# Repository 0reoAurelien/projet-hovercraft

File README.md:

# RAPPORT HOVERCRAFT

## Introduction

Un hovercraft (en français aéroglisseur) est un véhicule amphibie à portance aérostatique et à propulsion aérienne, qui en général possède une ou plusieurs hélices aériennes. La portance est assurée par un coussin d'air sous faible pression relative, entretenu par une soufflante à l'intérieur d'une enceinte dont les parois latérales, appelées jupes, sont suffisamment déformables pour suivre au plus près le relief de la surface survolée et ainsi réduire les fuites. Les aéroglisseurs se déplacent le plus souvent sur la mer, mais aussi sur toute surface terrestre ne présentant pas d'obstacles importants.

Nous avons ainsi pour but d'en réaliser un avec le matériel proposé.

## Analyse technique du problème posé

|Objectifs à remplir|Contraintes|
|-------------------|-----------|
|Avancer, décoller|Pas de contrôle à distance (autonome)|
|Avancer "droit"|Pas de contrôle à distance (autonome)|
|Avancer 10m|Pas de contrôle à distance (autonome)|
|Avancer 10m le plus rapidement possible|Pas de contrôle à distance (autonome)|

Nous avons utilisé les composants suivants :
* 2 régulateurs de tension BUCK MAX5033 qui ont un fort rendement (entre 80 et 90%)
* Une centrale inertielle MPU6050
* Un microprocesseur STM32 qui communique en I2C avec la centrale inertielle
* 2 ESC qui communique en PWM avec le microprocesseur, les ESC contrôlent 2 moteurs
* Une batterie qui délivre une tension de 11,1 V
* Une sonde de programmation
* Un servo-moteur XL320 qui communique en UART avec le microprocesseur

Nous employons des régulateurs de tension afin d'adapter les niveaux de tension pour les composants utilisés. Le microprocesseur nécessite une tension de 3,3 V, tandis que la sonde de programmation requiert 7,4 V. Cependant, la batterie fournit une tension de 11,1 V.
Le microprocesseur lui sert à contrôler les ESC et donc les moteurs pour qu'on puisse accomplir les objectifs fixés. Le microprocesseur est complété par l'ajout du servo-moteur pour l'asservissement.
On a alors ce [diagramme](https://github.com/0reoAurelien/projet-hovercraft/blob/main/Hardware/DIAGRAMME_VF.png) qui résume cela.

L'I2C et l'UART sont des protocoles de communication. L'UART permet l'échange de données entre un émetteur et un récepeteur dans les 2 sens et l'I2C permet à un système maître de controler des systèmes esclaves.

## Méthodologie

Pour mener à bien ce projet, nous avons eu à utiliser plusieurs logiciels : 
* **Github** : logiciel qui nous permet de rassembler toute nos travaux dans un seul endroit
* **Draw.io** : logiciel qui nous permet de tracer des graphes
* **Redmine** : logiciel qui nous permet de nous créer un emploi du temps (diagramme de Gantt) et nous a permis de nous répartir les différentes taches
* **Kicad** : logiciel qui nous permet de faire nos schematic ainsi que nos PCB
* **STM32CubeIDE** : logiciel qui nous permet de programmer notre microprocesseur

Nous avons décidé de nous séparer en 2 groupes, un qui s'occupe de la partie hardware (conception de PCB et soudure) et l'autre qui s'occupe de la partie software.

## Problèmes rencontrés

Lorsque nous avons commencé à souder l'un de nos PCB, il y avait un problème de court-circuit entre la masse et du 3V3. Ce problème a pu être révélé grâce à la caméra thermique. Nous avons analysé notre PCB et déterminé qu'il s'agissait d'un défaut à la fabrication de la carte. Nous avons pu corriger le problème en coupant une zone du PCB pour retirer le court-circuit. Cependant nous avions aussi oublié le connecteur qui alimentait le système en 3V3 donc nous avons donc dû refaire une V2 de notre deuxième PCB.

Par mégarde, nous avons arraché un connecteur ce qui a arraché une piste cuivre de notre PCB. Nous avons réparé le problème en repositionnant la connecteur et en soudant un fil à la place du circuit arraché.
Lors de la réalisation du 2ème PCB concernant les régulateurs, nous avons rencontré des problèmes lors de la conception (notamment l'optimisation de la taille et certaines empreintes) et lors de la soudure de certains composants.

Durant l'étape de programmation, nous nous sommes heurtés à de nombreuses difficultés notamment sur les différents pins de sortie.
Nous avons divisé notre code en plusieurs parties. Le programme de sélection du mode se trouve dans le main.c et permet de sélectionner l'un des 4 objectifs de notre hovercraft, puis de l'exécuter. Pour réalier cela, notre main.c faisait appel à plusieurs autres fichiers que nous avons réalisés dont le fichier functions.c chargé de gérer l'affichage du mode avec notre LED_USR, ainsi que de la lecture du bouton de sélection. Cette partie a pu être réalisée rapidement sans rencontrer de grandes difficultés. Les autres fichiers appelés devaient servir à commander les moteurs, gérer la centrale inertielle, et utiliser le servomoteur pour contrôler la trajectoire de l'aéroglisseur, mais nous avons fait face à plusieurs difficultés.
Le codage des pins en PWM, USART et en I2C n'ayant pas été traitées en TP de microprocesseurs, nous avons eu du mal à écrire les programmes.

En particulier, nous ne sommes pas parvenus à programmer les drivers des moteurs, qui nécessitent la génération de signaux PWM. Tester le code d'abord sur le PCB réalisé n'était pas une très bonne idée, car cela gênait l'identification de la cause lorsque le résultat n'est pas celui attendu. Nous pensons que le PCB était incapable de générer un signal PWM car, malgré une initialisation valide des pins en PWM, CubeMX indiquait toujours un conflit entre les pins associés aux PWM et nos connexions en I2C et GPIO. De plus, l'activation des moteurs nécessitait un processus précis (disponible sur la page 6 de la datasheet PICHLER_XQ_ESC.pdf), que l'on devait suivre en se basant uniquement sur des sons émis par les moteurs. Ce processus est celui qui doit permettre de fixer les valeurs hautes et basses de vitesse des moteurs. Comme nous manquions de temps et nous rencontrions des difficultés ici, nous avons du renoncer aux autres fonctionnalités liées à la centrale inertielle ou au servomoteur, afin d'augmenter l'effectif et concentrer nos efforts pour faire fonctionner les moteurs de l'aéroglisseur. Nous avions tout de même réalisé des recherches sur leur fonctionnement et trouvé des informations utiles concernant leur utilisation et leur programmation (la source (4) aurait pu servir).

Bien que nous avons obtenu des résultats sur l'alimentation pour la régulation de tension lorsque nous avons branché le PCB sur la batterie nous avons fait cramé certains composants (un condensateur, puis un régulateur après avoir remplacé le condensateur) mais nous ne savons pas pourquoi.
> Note : Tous nos [schémas Kicad](https://github.com/0reoAurelien/projet-hovercraft/tree/main/Hardware) et nos [codes](https://github.com/0reoAurelien/projet-hovercraft/tree/main/Software) sont disponibles sur notre github
## Résultats

Nous avons pu tester notre PCB à l'aide de différents programmes. Ainsi, le microprocesseur fonctionne correctement et fait très bien tourner la fonction de "menu de sélection" que nous avons écrite. Cette fonction atteste aussi du bon fonctionnement des communications GPIO car la carte est en mesure d'éclairer les LEDs et elle détecte nos appuis court et long sur le bouton de sélection.
Avec la carte Nucleo STM32H7A3Zi-Q utilisée en TP, nous avons réussi à émettre un signal PWM pour éclairer une led avec l'intensité souhaitée. 
Sur cette même carte, nous avons généré un signal PWM sur des pins de sortie et nous l'avons observé à l'oscilloscope. Nous avons ainsi testé 3 pins de la carte. L'un ne générait pas de signal, ceci peut être causé par une erreur de configuration sur CubeMX ou l'occupation du pin par une autre fonctionnalité; sur les deux autres, la génération de signal PWM était valide. En revanche, lors de la première observation, le signal affiché sur l'oscilloscope était déformé (ce défaut a disparu la séance suivante). Ceci peut être causé par un faux contact, ou un défaut des fils que nous avons utilisés pour le premier essai.

Photo du montage utilisé: [My image](PWMsurH7A3.jpg)

Nous avons ensuite testé ce signal sur le moteur (avec le régulateur XQ et une batterie 14V), cependant par mauvais choix de fréquence de signal PWM et/ou de consignes de démarrage dans le code, nous n'avons réussi qu'à entendre les bips provenant du moteur testé.

Nous avons réussi à programmer le driver des LEDs qui s'allument et suivent un pattern lorsque nous appuyons sur un bouton. Ce programme a pu être observé avec le PCB réalisé.

Concernant le PCB avec les régulateur de tension, on arrive à avoir la tension souhaitée en sortie avec une alimentation branchée sur le réseau. Cependant, lors des essais sur batteries, nous avons rencontrés des problèmes comme décrit dans la partie précédente.

Plus d'informations sur la partie Software sont disponibles dans le fichier Readme_Software.

## Développement durable

### Quelle réflexion avez-vous mené au cours de ce projet autour de la réutilisation d'éléments matériels pour la création de votre projet ?

Durant notre projet, nous avons beaucoup réfléchi à la réutilisation d'éléments matériels pour la création de notre Hovercraft. En effet, notre projet emploie des moteurs qui pourraient être réutilisés pour d'autres projets, et son support est fait à base de plastique recyclable (imprimé en 3D). Les hélices en plastique peuvent aussi être réutilisées pour concevoir des drones ou autres véhicules.

### Votre projet limite-t-il les quantités de pollutions ou de déchets rejetés dans les écosystèmes ?

Comme dit précédemment, notre projet est un Hovercraft, constitué d'un support imprimé 3D en plastique recyclable ainsi que de moteurs alimentés en électricité. Les batteries qui alimentent les moteurs sont rechargées via le réseau d'électricité de l'ENSEA. De plus, notre hovercraft ne consomme pas beaucoup d'électricité et ne rejette rien dans l'atmosphère ou dans les écosystèmes. Enfin, nous avons attaché une certaine importance à limiter le nombre de composants dans nos PCB. Nous souhaitions initialement utiliser deux boutons pour sélectionner les modes, puis exécuter le programme sélectionné. Au lieu de celà, nous n'avons utilisé qu'un bouton en distinguant les appuis courts et les appuis longs. De même, nous souhaitions utiliser 4 LEDs pour indiquer la fonction actuellement sélectionné. Nous avons réduit notre quantité de déchet en utilisant une seule LED que l'on fait clignoter n fois. Cela en fait un projet à empreinte carbone faible, et dont le nombre de déchets sera limité après sa fin de vie.

## Conclusion

Ce projet de Hovercraft a été une expérience enrichissante qui nous a permis d'explorer les aspects techniques de la création d'un véhicule autonome. Nous avons pris en compte des contraintes environnementales en minimisant notre utilisations de composants pour les PCB, en utilisant un plastique recyclable pour la coque du hovercraft, et nous avons pensé à la réutilisation future de certains composants tels que les moteurs.

Durant ce projet, nous avons été mis en conditions réélles, avec des objectifs à atteindre comme pour convenir à un cahier des charges. Nous avions un temps limité et nous devions produire un hovercraft capable de répondre à des exigences. Bien que nous ne soyons pas parvenus à réaliser un hovercraft fonctionnel, nous avons été en mesure de produire des PCB exploitables et de fournir un programme organisé afin de contrôler le véhicule. Cela a donc été une expérience véritablement enrichissante car nous avons pu, au fil des séances, affûter nos connaissances et avancer sur les différents objectifs tout en assurant une cohésion d'équipe. Ce travail en groupe nous a réellement permis d'améliorer notre communication ainsi que notre organisation. En effet, nous avons réparti les différentes tâches en suivant un diagramme de Gantt, que ce soit pour le software ou le hardware. Nous avons ainsi pu fixer des échéances et optimiser notre temps afin d'aller le plus loin possible dans ce projet. Nous n'avons malheureusement pas pu achever le projet comme nous l'avions espéré mais cela n'enlève pas les apprentissages que nous en avons tirés.

Finalement, malgré les difficultés rencontrées, ce projet nous a permis d'acquérir de précieuses compétences techniques, de prendre conscience des enjeux environnementaux et de développer notre esprit d'innovation et de collaboration. 
## Sources

(1):https://fr.wikipedia.org/wiki/Aéroglisseur

(2):https://stackoverflow.com/questions/43483762/using-stm32-hal-timer-and-adjusting-the-duty-cycle-of-a-pwm-signal

(3):https://moons.link/post-632/

(4):http://news.eeworld.com.cn/mcu/ic467303.html

(5):https://polybot-grenoble.fr/wiki/index.php?title=Guide_STM32CubeIDE&mobileaction=toggle_view_mobile

(6):https://www.youtube.com/watch?v=qUFhDOTz160

(7):http://matsubara-ui-design.net/2021/06/i2c/

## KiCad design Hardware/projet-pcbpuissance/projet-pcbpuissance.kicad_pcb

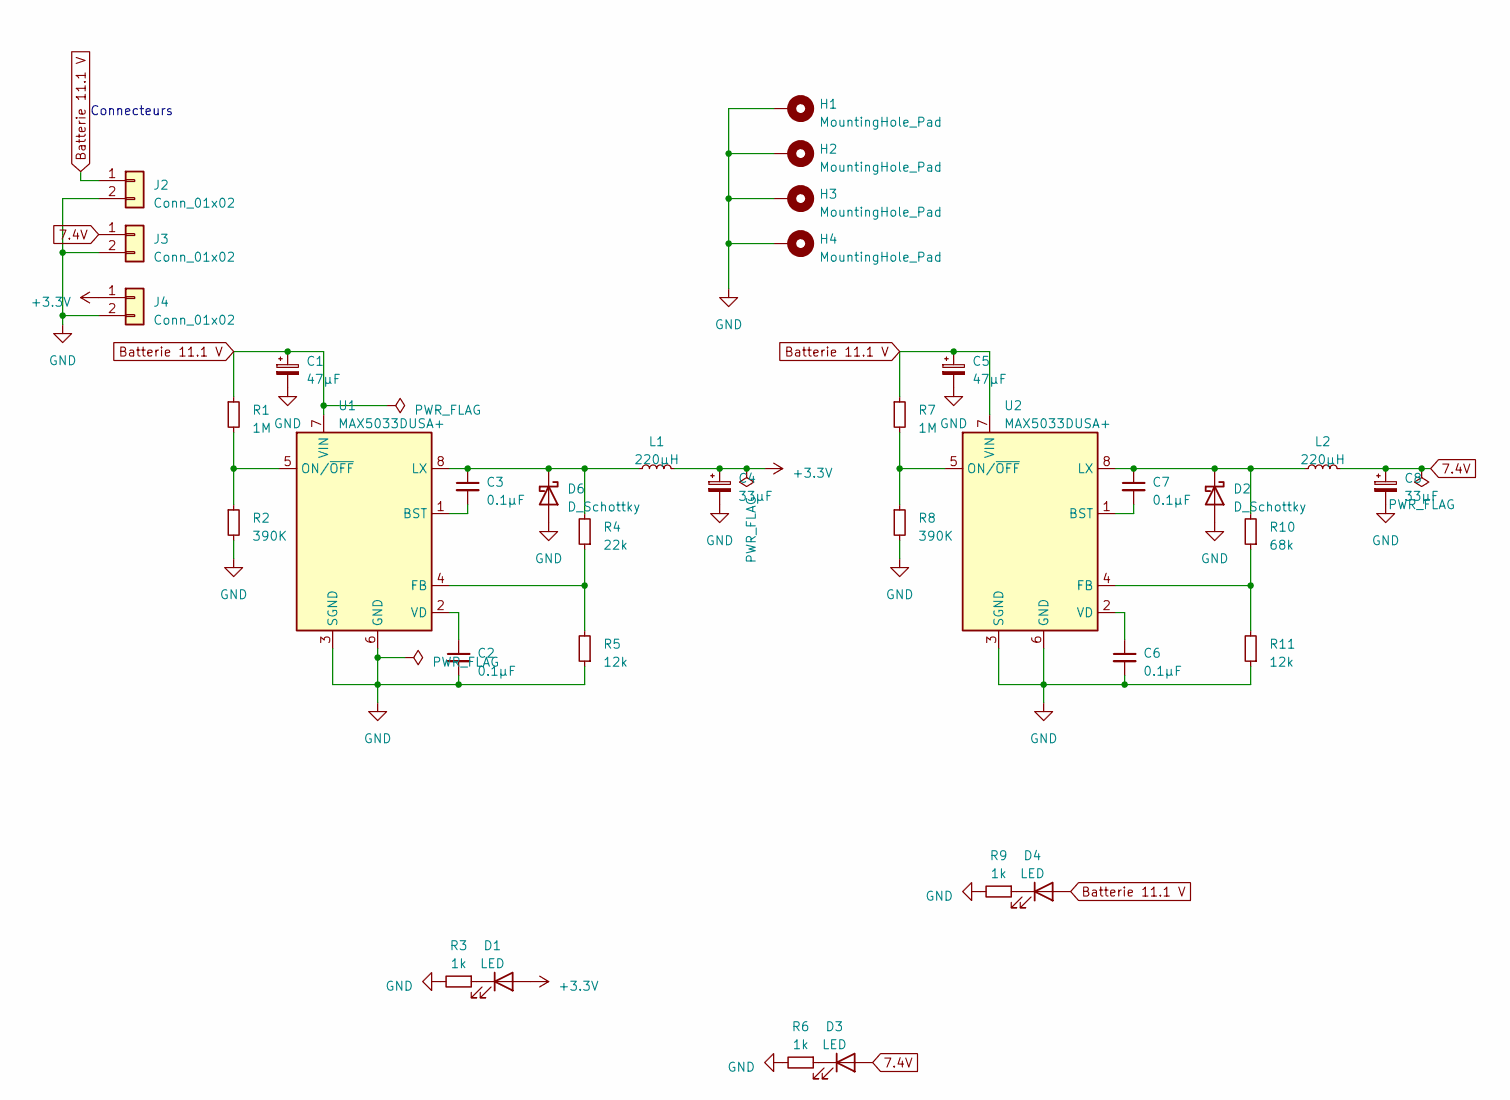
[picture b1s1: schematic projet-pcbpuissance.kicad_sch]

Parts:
C1, C5: 47µF; CP_Elec_6.3x7.7
C2, C3, C6, C7: 0.1µF; C_0603_1608Metric_Pad1.08x0.95mm_HandSolder
C4, C8: 33µF; CP_Elec_6.3x7.7
D1, D3, D4: LED; LED_0603_1608Metric_Pad1.05x0.95mm_HandSolder
D2, D6: D_Schottky; D_2114_3652Metric_Pad1.85x3.75mm_HandSolder
H1, H2, H3, H4: MountingHole_Pad; MountingHole_3.2mm_M3_DIN965_Pad
J2, J3, J4: Conn_01x02; JST_XH_B2B-XH-A_1x02_P2.50mm_Vertical
L1, L2: 220µH; L_12x12mm_H6mm
R1, R7: 1M; R_0603_1608Metric_Pad0.98x0.95mm_HandSolder
R2, R8: 390K; R_0603_1608Metric_Pad0.98x0.95mm_HandSolder
R3, R6, R9: 1k; R_0603_1608Metric_Pad0.98x0.95mm_HandSolder
R4: 22k; R_0603_1608Metric_Pad0.98x0.95mm_HandSolder
R5, R11: 12k; R_0603_1608Metric_Pad0.98x0.95mm_HandSolder
R10: 68k; R_0603_1608Metric_Pad0.98x0.95mm_HandSolder
U1, U2: MAX5033DUSA+; Diodes_PSOP-8

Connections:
7.4V: C8.1, D3.2 (A), J3.1, L2.2
+3.3V: C4.1, D1.2 (A), J4.1, L1.2
Batterie 11.1 V: C1.1, C5.1, D4.2 (A), J2.1, R1.1, R7.1, U1.7 (VIN), U2.7 (VIN)
GND: C1.2, C2.2, C4.2, C5.2, C6.2, C8.2, D2.2 (A), D6.2 (A), H1.1, H2.1, H3.1, H4.1, J2.2, J3.2, J4.2, R2.2, R3.2, R5.1, R6.2, R8.2, R9.2, R11.1, U1.3 (SGND), U1.6 (GND), U2.3 (SGND), U2.6 (GND)
unnamed: D1.1 (K), R3.1
unnamed: C7.1, D2.1 (K), L2.1, R10.2, U2.8 (LX)
unnamed: D3.1 (K), R6.1
unnamed: D4.1 (K), R9.1
unnamed: C3.1, D6.1 (K), L1.1, R4.2, U1.8 (LX)
unnamed: C3.2, U1.1 (BST)
unnamed: R4.1, R5.2, U1.4 (FB)
unnamed: R1.2, R2.1, U1.5 (ON/~OFF)
unnamed: C2.1, U1.2 (VD)
unnamed: C7.2, U2.1 (BST)
unnamed: R10.1, R11.2, U2.4 (FB)
unnamed: R7.2, R8.1, U2.5 (ON/~OFF)
unnamed: C6.1, U2.2 (VD)

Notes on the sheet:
Connecteurs

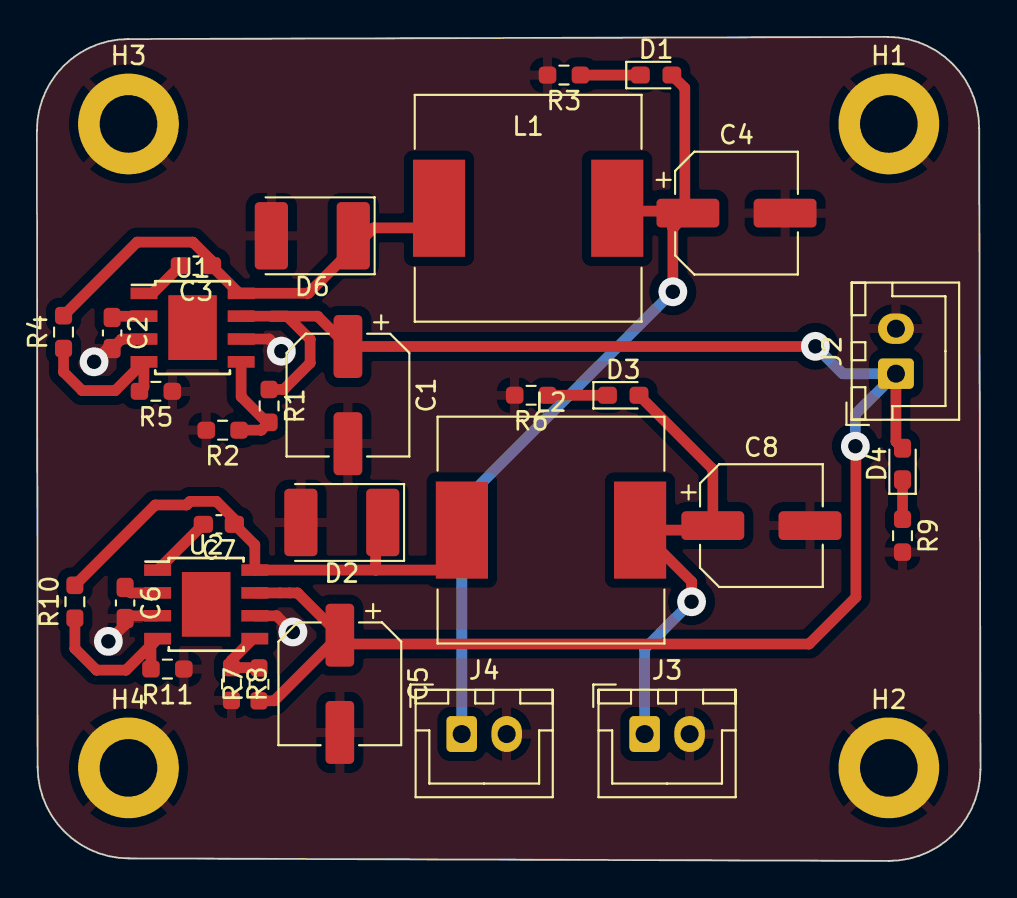
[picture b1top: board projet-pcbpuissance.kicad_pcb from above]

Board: 2 copper layers, 52.4 x 45.8 mm, 35 parts (0 on the bottom side), 17 nets.

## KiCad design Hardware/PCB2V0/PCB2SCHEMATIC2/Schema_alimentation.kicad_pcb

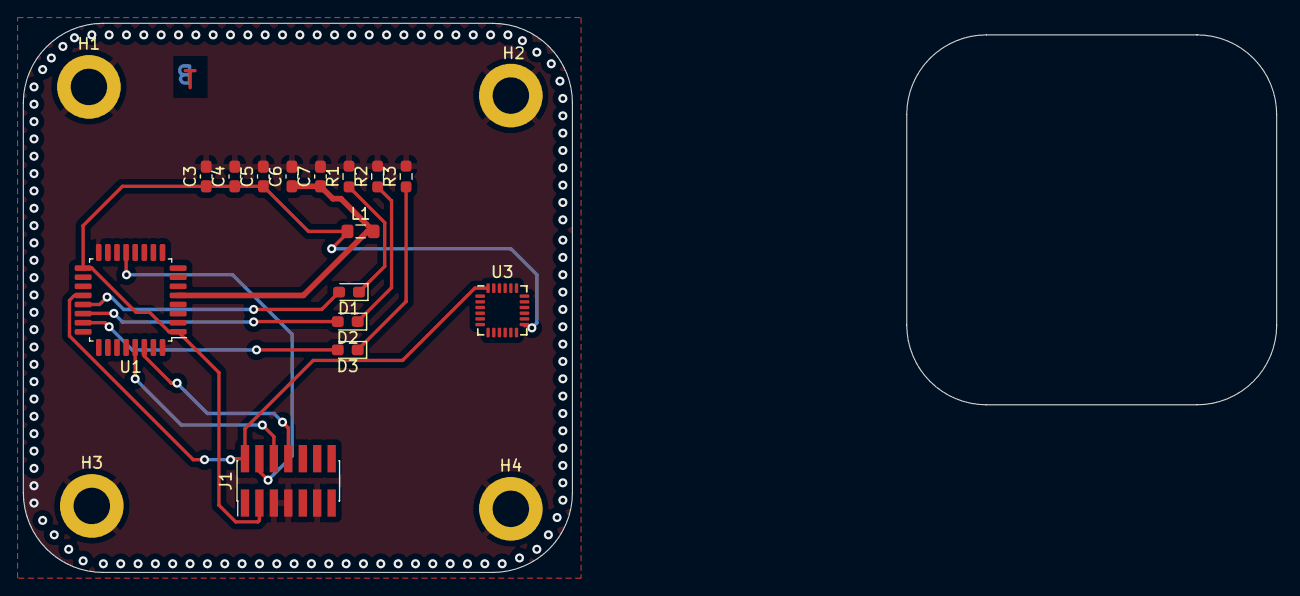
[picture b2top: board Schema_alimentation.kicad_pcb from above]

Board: 2 copper layers, 110.2 x 48.3 mm, 19 parts (0 on the bottom side), 13 nets.

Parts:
C3: 4u7; C_0603_1608Metric_Pad1.08x0.95mm_HandSolder
C4, C5: 100n; C_0603_1608Metric_Pad1.08x0.95mm_HandSolder
C6: 1u; C_0603_1608Metric_Pad1.08x0.95mm_HandSolder
C7: 10n; C_0603_1608Metric_Pad1.08x0.95mm_HandSolder
D1, D2, D3: LED_Small; LED_0603_1608Metric_Pad1.05x0.95mm_HandSolder
H1, H2, H3, H4: MountingHole_Pad; MountingHole_3.2mm_M3_DIN965_Pad
J1: Conn_02x07_Odd_Even; PinHeader_2x07_P1.27mm_Vertical_SMD
L1: 39n; L_0805_2012Metric_Pad1.05x1.20mm_HandSolder
R1, R2, R3: 1k; R_0603_1608Metric_Pad0.98x0.95mm_HandSolder
U1: STM32L412KBTx; LQFP-32_7x7mm_P0.8mm
U3: MPU-6050; InvenSense_QFN-24_4x4mm_P0.5mm

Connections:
+3.3V: C3.1, C4.1, C5.1, J1.3, L1.1, U1.1 (VDD), U1.17 (VDD), U3.13 (VDD)
+3.3VA: C6.1, C7.1, L1.2, U1.5 (VDDA)
BOUTON_RESET: J1.8, U1.30 (PB7)
BOUTON_USR: J1.6, U1.29 (PB6)
GND: C3.2, C4.2, C5.2, C6.2, C7.2, H1.1, H2.1, H3.1, H4.1, J1.5, J1.7, J1.11, R1.2, R2.2, R3.2, U1.16 (VSS), U1.32 (VSS), U3.18 (GND)
LED_PWR: D1.2 (A), U1.21 (PA11)
LED_USER1: D2.2 (A), U1.22 (PA12)
LED_USER2: D3.2 (A), U1.23 (PA13)
unnamed: D1.1 (K), R1.1
unnamed: D2.1 (K), R2.1
unnamed: D3.1 (K), R3.1
SCL: J1.4, U1.13 (PA7), U3.23 (SCL)
SDA: J1.2, U1.20 (PA10), U3.24 (SDA)

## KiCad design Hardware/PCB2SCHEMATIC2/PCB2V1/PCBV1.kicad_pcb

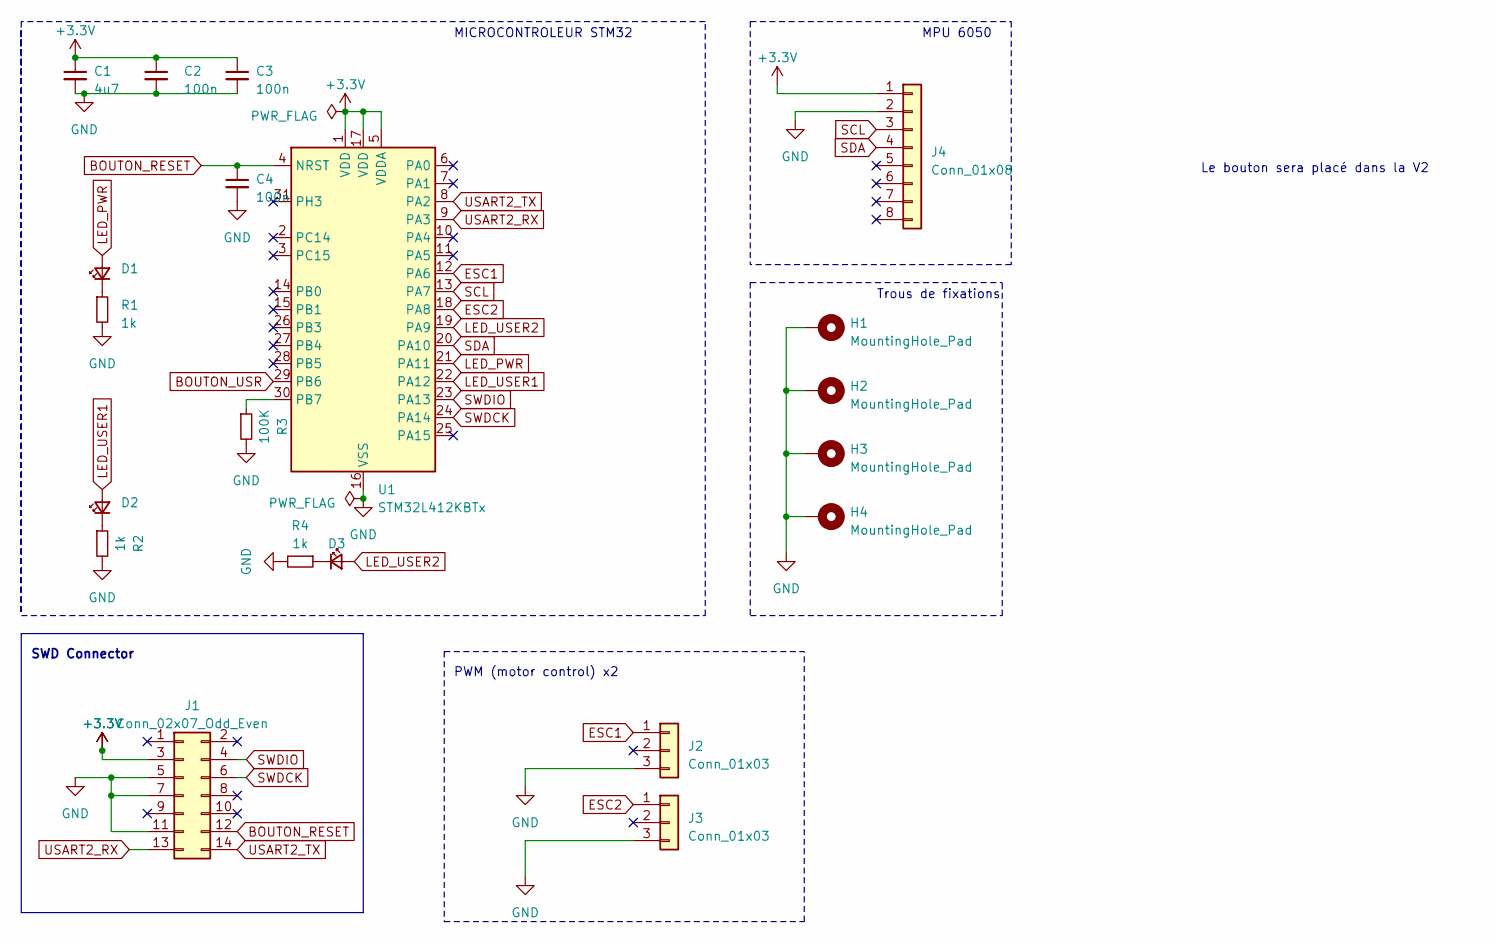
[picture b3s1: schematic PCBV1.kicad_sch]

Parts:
C1: 4u7; C_0603_1608Metric_Pad1.08x0.95mm_HandSolder
C2, C3, C4: 100n; C_0603_1608Metric_Pad1.08x0.95mm_HandSolder
D1, D2, D3: LED_Small; LED_0603_1608Metric_Pad1.05x0.95mm_HandSolder
H1, H2, H3, H4: MountingHole_Pad; MountingHole_3.2mm_M3_DIN965_Pad
J1: Conn_02x07_Odd_Even; PinHeader_2x07_P1.27mm_Vertical_SMD
J2, J3: Conn_01x03; JST_XH_B3B-XH-A_1x03_P2.50mm_Vertical
J4: Conn_01x08; JST_XH_B8B-XH-A_1x08_P2.50mm_Vertical
R1, R2, R4: 1k; R_0603_1608Metric_Pad0.98x0.95mm_HandSolder
R3: 100K; R_0603_1608Metric_Pad0.98x0.95mm_HandSolder
U1: STM32L412KBTx; LQFP-32_7x7mm_P0.8mm

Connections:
+3.3V: C1.1, C2.1, C3.1, J1.3, J4.1, U1.1 (VDD), U1.5 (VDDA), U1.17 (VDD)
BOUTON_RESET: C4.1, J1.12, U1.4 (NRST)
BOUTON_USR: U1.29 (PB6)
ESC1: J2.1, U1.12 (PA6)
ESC2: J3.1, U1.18 (PA8)
GND: C1.2, C2.2, C3.2, C4.2, H1.1, H2.1, H3.1, H4.1, J1.5, J1.7, J1.11, J2.3, J3.3, J4.2, R1.2, R2.2, R3.2, R4.2, U1.16 (VSS), U1.32 (VSS)
LED_PWR: D1.2 (A), U1.21 (PA11)
LED_USER1: D2.2 (A), U1.22 (PA12)
LED_USER2: D3.2 (A), U1.19 (PA9)
unnamed: D1.1 (K), R1.1
unnamed: D2.1 (K), R2.1
unnamed: D3.1 (K), R4.1
unnamed: R3.1, U1.30 (PB7)
SCL: J4.3, U1.13 (PA7)
SDA: J4.4, U1.20 (PA10)
SWDCK: J1.6, U1.24 (PA14)
SWDIO: J1.4, U1.23 (PA13)
USART2_RX: J1.13, U1.9 (PA3)
USART2_TX: J1.14, U1.8 (PA2)

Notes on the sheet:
PWM (motor control) x2
MPU 6050
Le bouton sera placé dans la V2
Trous de fixations
MICROCONTROLEUR STM32
SWD Connector

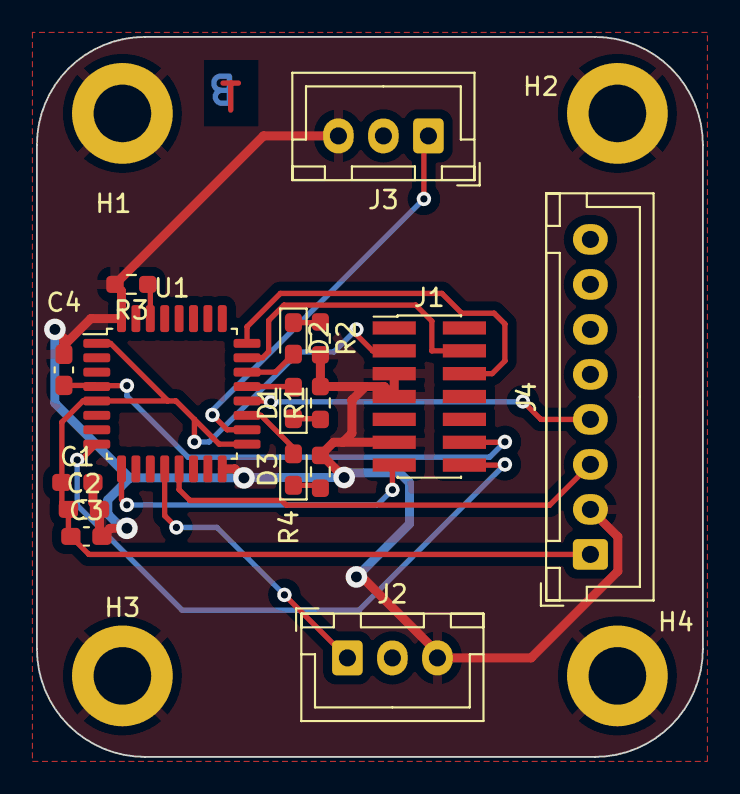
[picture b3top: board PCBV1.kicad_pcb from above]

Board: 2 copper layers, 37.0 x 40.0 mm, 20 parts (0 on the bottom side), 18 nets.

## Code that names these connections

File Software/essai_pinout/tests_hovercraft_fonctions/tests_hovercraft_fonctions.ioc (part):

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Mcu.Name=STM32L412KBTx
Mcu.Package=LQFP32
Mcu.UserName=STM32L412KBTx
PA10.Mode=I2C
PA10.Signal=I2C1_SDA
PA11.GPIOParameters=GPIO_Label
PA11.GPIO_Label=LED_1
PA11.Signal=GPIO_Output
PA12.GPIOParameters=GPIO_Label
PA12.GPIO_Label=LED_2
PA12.Signal=GPIO_Output
PA13\ (JTMS/SWDIO).Mode=Serial_Wire
PA13\ (JTMS/SWDIO).Signal=SYS_JTMS-SWDIO
PA14\ (JTCK/SWCLK).Mode=Serial_Wire
PA14\ (JTCK/SWCLK).Signal=SYS_JTCK-SWCLK
PA2.Mode=Asynchronous
PA2.Signal=USART2_TX
PA3.Mode=Asynchronous
PA3.Signal=USART2_RX
PA6.Signal=S_TIM16_CH1
PA8.Signal=S_TIM1_CH1
PA9.Mode=I2C
PA9.Signal=I2C1_SCL
PB6.GPIOParameters=GPIO_PuPd
PB6.GPIO_PuPd=GPIO_PULLUP
PB6.Signal=GPIO_Input
RCC.HSE_VALUE=8000000
RCC.SYSCLKFreq_VALUE=80000000
RCC.SYSCLKSource=RCC_SYSCLKSOURCE_PLLCLK
board=custom

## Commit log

2023-04-03 test
    c'est un test
2023-04-03 Datasheets
2023-04-03 Ajout de main.c
2023-04-03 Suppression de main.c
2023-04-03 Added Untitled Diagram.drawio
2023-04-03 Ajouté(e) Diagramme sans nom.drawio
2023-04-03 Schéma-bloc asservissement
2023-04-03 Mettre à jour Untitled Diagram.drawio
2023-04-03 Mettre à jour Diagramme sans nom.drawio
2023-04-04 Chaine d'energie/informative.drawio
2023-04-07 add folders
2023-04-10 Schéma-bloc Hovercraft.drawio
2023-04-10 Schéma-bloc.drawio*
2023-04-10 Rename Diagramme sans nom.drawio to Diagramme_Energie.drawio
2023-04-10 Create Fonctions_Hovercraft
    liste des fonctions nécessaires pour le projet
2023-04-10 Mettre à jour Diagramme_Energie.drawio
2023-04-10 Rename Diagramme_Energie.drawio to Hardware/Diagramme_Energie.drawio
2023-04-10 Update Fonctions_Hovercraft
2023-04-10 Rename Fonctions_Hovercraft to Software/Fonctions_Hovercraft
2023-04-11 Add files via upload
    Liste de l'ensemble des fonctions que nous programmerons et utiliserons pour notre projet. Il manque pour le moment les fontions chargées de lire les boutons, ainsi que les fonctions chargées de trai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
2023-04-11 Create SelectMode
    On écrit une fonction SelectMode afin de pouvoir choisir quel mode l'utilisateur veut utiliser
2023-04-11 Create Main.c
    On écrit une fonction main.c afin de pouvoir utiliser les fonctions créées
2023-04-11 Update SelectMode
2023-04-11 Update SelectMode
    ajout d'un commentaire
2023-04-11 Add files via upload
    update de la fonction SelectMode
2023-04-11 Create Forward
    création de la fonction forward
2023-04-11 Create ForwardFront
    création de la fonction ForwardFront
2023-04-11 Create Forward10
    création de la fonction Forward10
2023-04-11 Create ForwardFast
    création de la fonction ForwardFast
2023-04-11 update odt
2023-04-11 Create README.md
    création d'un readme
2023-04-11 Add README_SOFTWARE to explain how our software project will work
2023-04-11 Update README_SOFTWARE.md
    Ajout des fonctions principales nécessaires pour le projet
2023-04-11 Update README_SOFTWARE.md
    ajout de la fonction SelectMode
2023-04-11 Update README_SOFTWARE.md
    ajout des prototypes des fonctions
2023-04-11 Create README_SOFTWARE.md
    ajout des fonctions main, et de la version SelectMode à un seul bouton
2023-04-11 Update README_SOFTWARE.md
    rajout des prototypes des fonctions
2023-04-11 Update README_SOFTWARE.md
    modification des prototypes de fonctions
2023-04-15 ajout des fonctionnalités d'affichage du mode (en utilisant les deux voyants LED USR à disposition)
2023-04-16 Add files via upload
    Projet KiCad + captures d'écran
2023-04-17 correction
2023-04-26 Rename Schema alimentation.kicad_pcb to Schema_alimentation.kicad_pcb
2023-04-26 Rename Schema alimentation.kicad_sch to Schema_alimentation.kicad_sch
2023-04-26 Rename Schema alimentation.kicad_pro to Schema_alimentation.kicad_pro
2023-04-26 Rename Schema alimentation.kicad_prl to Schema_alimentation.kicad_prl
2023-04-26 Rename Hardware/PCB2:SCHEMATIC2/PCB2:SCHEMATIC2/Schema_alimentation.kicad_pcb to Hardware/PCB2SCHEMATIC2/PCB2SCHEMATIC2/Schema_alimentation.kicad_pcb
2023-04-26 Rename Hardware/PCB2SCHEMATIC2/PCB2SCHEMATIC2/Schema_alimentation.kicad_pcb to Hardware/PCB2:SCHEMATIC2/PCB2:SCHEMATIC2/Schema_alimentation.kicad_pcb
2023-04-27 Modification nom de dossier
2023-04-28 Modification pcb-puissance
2023-04-29 Modif
2023-04-29 Modification pcb puissance
2023-04-29 Modif pcb-puissance
2023-04-30 Modif pcb puissance
2023-05-01 Modif pcb puisance
2023-05-02 Create PCB2V1
2023-05-02 message
2023-05-09 Projet sur STM32CubeIDE
    Creation du projet et reglage des pins pour sortie PWN
2023-05-09 pwm pinout
2023-05-09 led pinout
2023-05-09 Réglage des pins sur la carte STM32
    Les pins de la carte STM32L412KBT6 ont été réglés en accord avec le PCB et afin de pouvoir communiquer en PWM et ainsi contrôler les moteurs
2023-05-15 ajout du TP4 comme ressource
2023-05-15 code essai moteur
2023-05-15 Modif pcb
2023-05-15 essai
2023-05-15 Modif(en cours)
2023-05-15 ajout test
2023-05-19 update with bigger vias and fix unrouted tracks
2023-05-22 Update hovercraft_test1.c
    adaptation du programme à notre test et correction de bugs mineurs
2023-05-22 hovercraft_test1.h
    prototypage des fonctions du fichier de test
2023-05-22 version fonction externe
2023-05-22 ajout argument test
2023-05-22 update test
2023-05-23 modification de configuration
2023-05-23 Realisation de tests du PCB 1
    Les tests des LEDs, du bouton et du code sont validés
2023-05-23 Update README.md
    Réponse à une des questions concernant le développement durable
2023-05-29 update des fonctions
    update des fonctions pour les tests de mardi 30 mai
2023-05-29 adaptation au nouveau PCB
    mise en place de nouveaux tests adaptés à la nouvelle version du PCB (nouveaux ports)
2023-05-29 Update programme
    J'ai fini de convertir le programme pour l'adapter au nouveau PCB de Vincent. Je me suis beaucoup appuyé sur ce qu'avait fait Laurine pour qu'on ait les mêmes configurations des pins de la carte (not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
2023-05-30 Update README.md
    Rajout des problèmes rencontrés et des résultats
2023-05-30 Update README.md
    Réponses aux questions de développement durable
2023-05-30 sources
2023-05-30 source
2023-05-30 retrait du reminder
2023-06-02 code
2023-06-02 Mise en place du programme général
    La boucle main contient maintenant la structure générale du code, testée au préalable. De plus, il inclut les tests des moteurs avec affichage de leds pour vérifier l'état de fonctionnement
2023-06-02 update essai_pinout
    ajustement mineur du programme général
2023-06-06 Modif schéma
2023-06-06 essai H7A3
2023-06-07 commentaires
2023-06-07 readme
2023-06-09 Update README.md
    orthographe lignes 0 à 50
2023-06-09 Update README.md
    sauvegarde rapide des changements
2023-06-09 Update README.md
    Ajout de nouveaux éléments, corrections de formulations
2023-06-09 Update README.md
    update conclusion
2023-06-09 Update README.md
    Touche finale de la conclusion
2023-06-09 Update README_SOFTWARE.md
    touche final du readme software
